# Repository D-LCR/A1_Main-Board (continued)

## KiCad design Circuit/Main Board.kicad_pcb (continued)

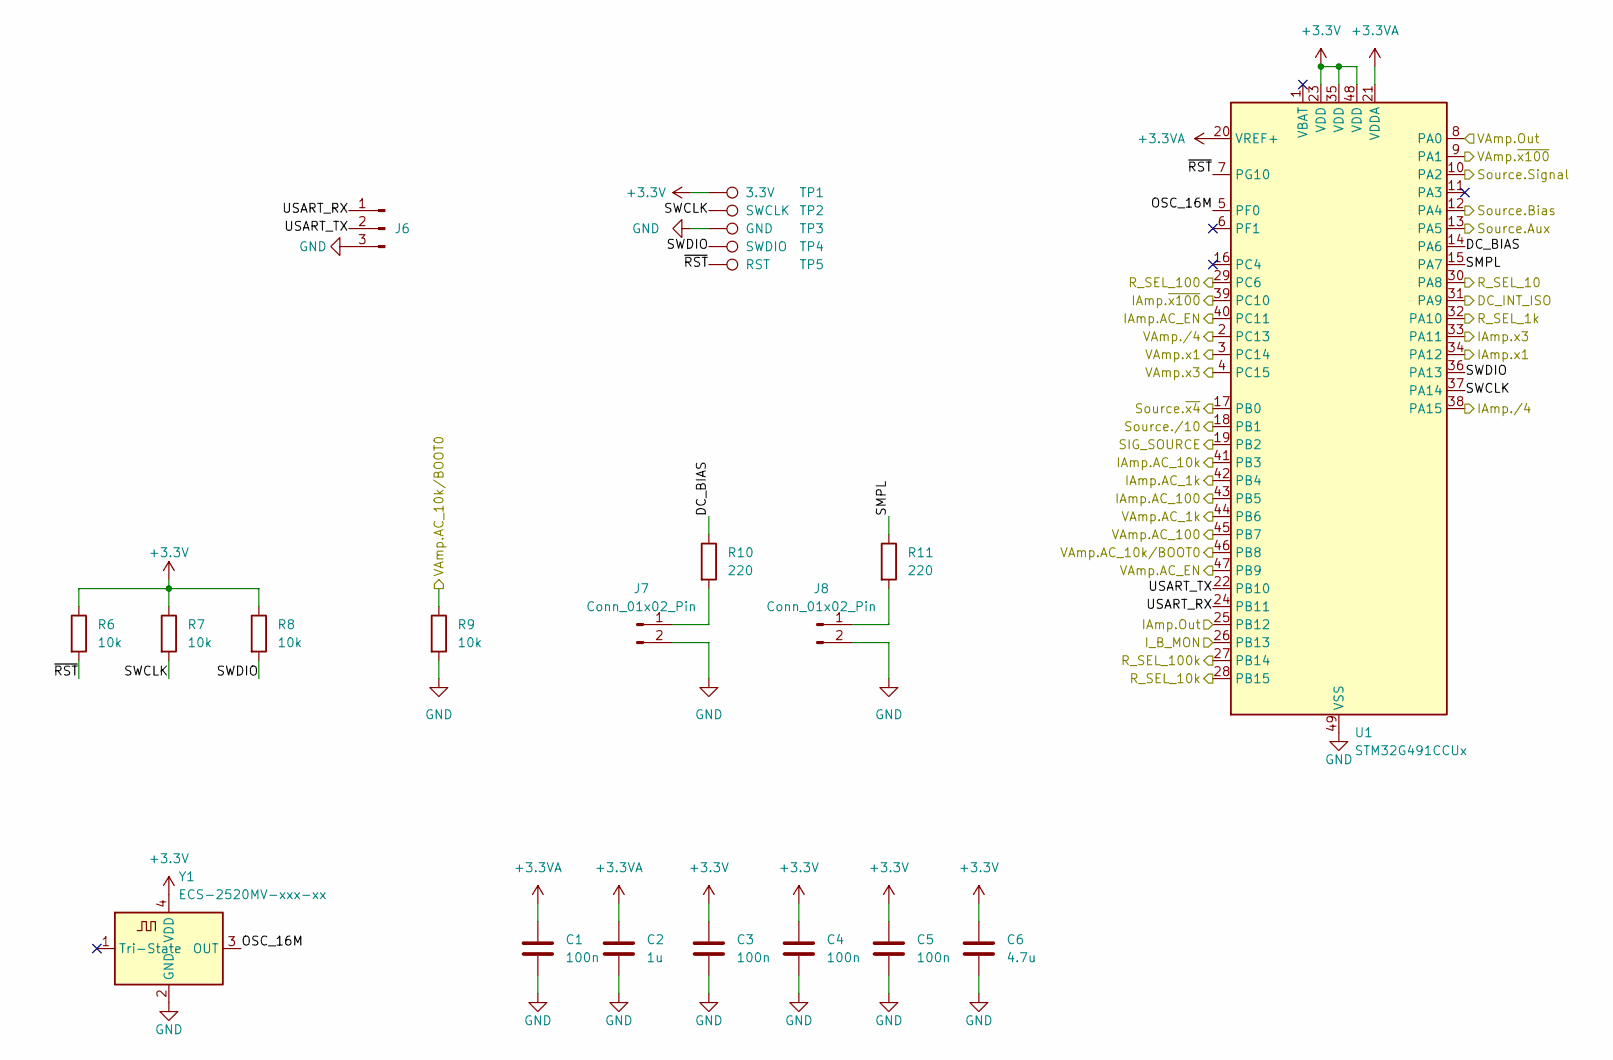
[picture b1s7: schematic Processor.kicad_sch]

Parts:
C1, C3, C4, C5: 100n; C_0805_2012Metric
C2: 1u; C_0805_2012Metric
C6: 4.7u; C_0805_2012Metric
J6: Conn_01x03_Pin; Molex_KK-254_AE-6410-03A_1x03_P2.54mm_Vertical
J7, J8: Conn_01x02_Pin; Molex_KK-254_AE-6410-02A_1x02_P2.54mm_Vertical
R6, R7, R8, R9: 10k; R_0805_2012Metric
R10, R11: 220; R_0805_2012Metric
TP1: 3.3V; TestPoint_Pad_2.0x2.0mm
TP2: SWCLK; TestPoint_Pad_2.0x2.0mm
TP3: GND; TestPoint_Pad_2.0x2.0mm
TP4: SWDIO; TestPoint_Pad_2.0x2.0mm
TP5: RST; TestPoint_Pad_2.0x2.0mm
U1: STM32G491CCUx; QFN-48-1EP_7x7mm_P0.5mm_EP5.6x5.6mm
Y1: ECS-2520MV-xxx-xx; Oscillator_SMD_ECS_2520MV-xxx-xx-4Pin_2.5x2.0mm

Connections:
+3.3V: C3.1, C4.1, C5.1, C6.1, R6.1, R7.1, R8.1, TP1.1 (1_1), U1.23 (VDD), U1.35 (VDD), U1.48 (VDD), Y1.4 (VDD); also elsewhere on the board
+3.3VA: C1.1, C2.1, U1.20 (VREF+), U1.21 (VDDA); also elsewhere on the board
/Auto-Balancing Bridge/AC_1k: U1.43 (PB5); also elsewhere on the board
/Auto-Balancing Bridge/AC_10k: U1.41 (PB3); also elsewhere on the board
/Auto-Balancing Bridge/AC_100: U1.42 (PB4); also elsewhere on the board
/Auto-Balancing Bridge/AC_EN: U1.40 (PC11); also elsewhere on the board
/Auto-Balancing Bridge/DC_INT_ISO: U1.31 (PA9); also elsewhere on the board
/Auto-Balancing Bridge/I_B_MONITOR: U1.26 (PB13); also elsewhere on the board
/Auto-Balancing Bridge/R_SEL_1k: U1.32 (PA10); also elsewhere on the board
/Auto-Balancing Bridge/R_SEL_10: U1.30 (PA8); also elsewhere on the board
/Auto-Balancing Bridge/R_SEL_10k: U1.28 (PB15); also elsewhere on the board
/Auto-Balancing Bridge/R_SEL_100: U1.29 (PC6); also elsewhere on the board
/Auto-Balancing Bridge/R_SEL_100k: U1.27 (PB14); also elsewhere on the board
/Current Amplifier/Out: U1.25 (PB12); also elsewhere on the board
/Current Amplifier/x1: U1.34 (PA12); also elsewhere on the board
/Current Amplifier/x3: U1.33 (PA11); also elsewhere on the board
/Current Amplifier//4: U1.38 (PA15); also elsewhere on the board
/Current Amplifier/~x100: U1.39 (PC10); also elsewhere on the board
/Processor/DC_BIAS: R10.1, U1.14 (PA6)
/Processor/OSC_16M: U1.5 (PF0), Y1.3 (OUT)
/Processor/SIG_SOURCE: U1.19 (PB2); also elsewhere on the board
/Processor/SMPL: R11.1, U1.15 (PA7)
/Processor/SWCLK: R7.2, TP2.1 (1_1), U1.37 (PA14)
/Processor/SWDIO: R8.2, TP4.1 (1_1), U1.36 (PA13)
/Processor/Source.Aux: U1.13 (PA5); also elsewhere on the board
/Processor/Source.Bias: U1.12 (PA4); also elsewhere on the board
/Processor/Source.Signal: U1.10 (PA2); also elsewhere on the board
/Processor/Source./10: U1.18 (PB1); also elsewhere on the board
/Processor/Source.~x4: U1.17 (PB0); also elsewhere on the board
/Processor/USART_RX: J6.1, U1.24 (PB11)
/Processor/USART_TX: J6.2, U1.22 (PB10)
/Processor/VAmp.AC_1k: U1.44 (PB6); also elsewhere on the board
/Processor/VAmp.AC_10k/BOOT0: R9.1, U1.46 (PB8); also elsewhere on the board
/Processor/VAmp.AC_100: U1.45 (PB7); also elsewhere on the board
/Processor/VAmp.AC_EN: U1.47 (PB9); also elsewhere on the board
/Processor/VAmp.Out: U1.8 (PA0); also elsewhere on the board
/Processor/VAmp.x1: U1.3 (PC14); also elsewhere on the board
/Processor/VAmp.x3: U1.4 (PC15); also elsewhere on the board
/Processor/VAmp./4: U1.2 (PC13); also elsewhere on the board
/Processor/VAmp.~x100: U1.9 (PA1); also elsewhere on the board
/Processor/~RST: R6.2, TP5.1 (1_1), U1.7 (PG10)
GND: C1.2, C2.2, C3.2, C4.2, C5.2, C6.2, J6.3, J7.2, J8.2, R9.2, TP3.1 (1_1), U1.49 (VSS), Y1.2 (GND); also elsewhere on the board
unnamed: J7.1, R10.2
unnamed: J8.1, R11.2

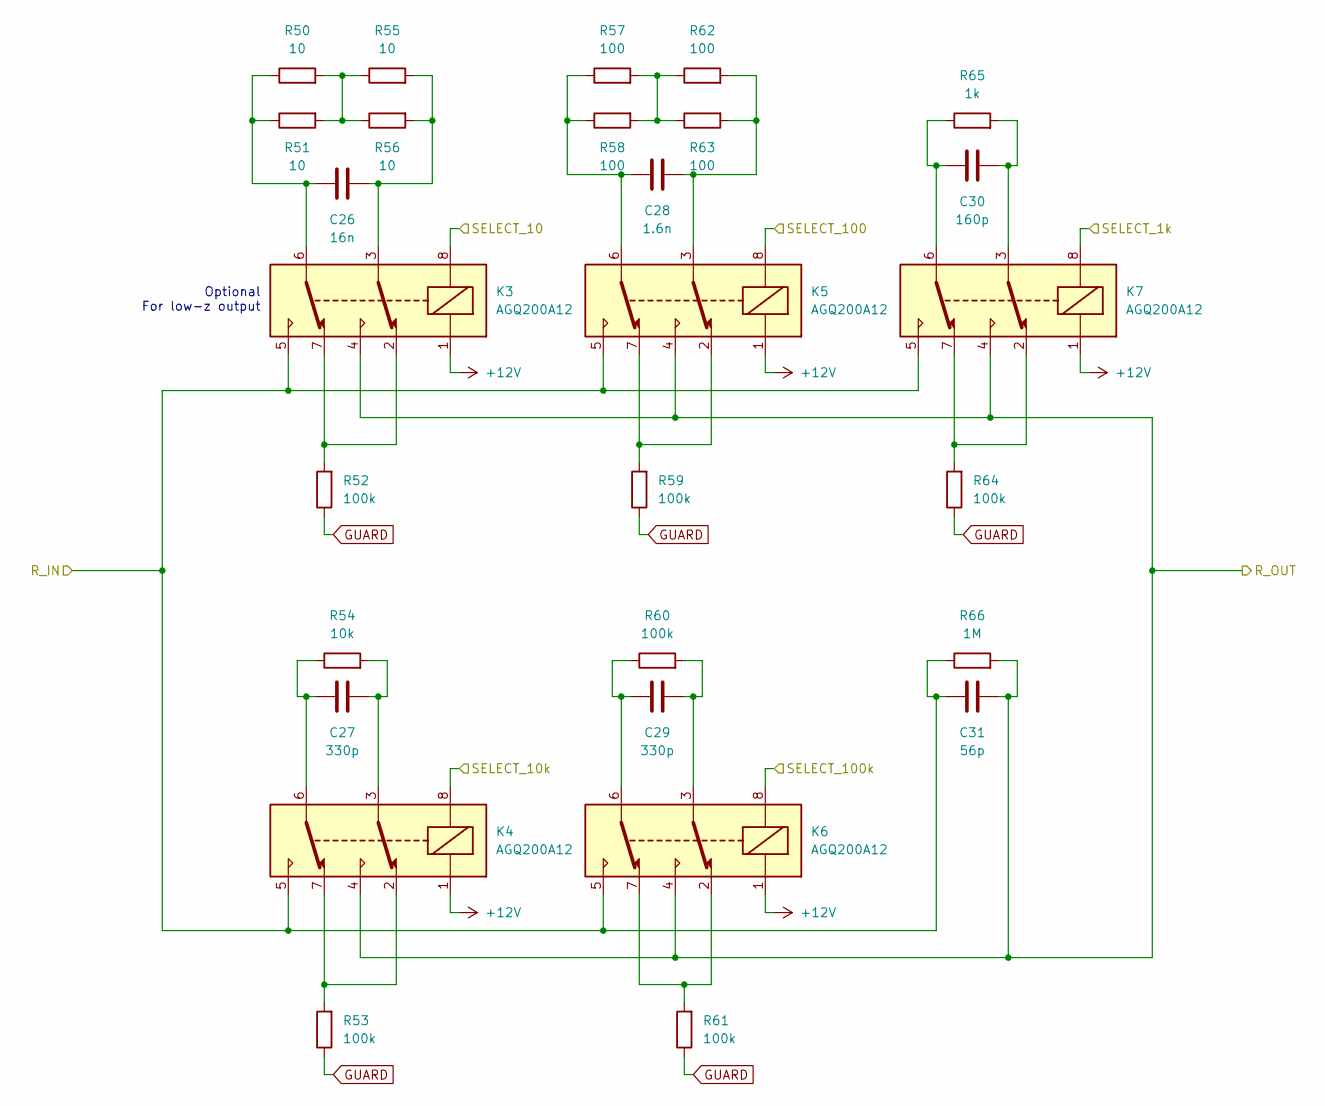
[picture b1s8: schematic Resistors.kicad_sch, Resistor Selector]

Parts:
C26: 16n; C_0805_2012Metric
C27, C29: 330p; C_0805_2012Metric
C28: 1.6n; C_0805_2012Metric
C30: 160p; C_0805_2012Metric
C31: 56p; C_0805_2012Metric
K3, K4, K5, K6, K7: AGQ200A12; RELAY_AGQ_A_PAN; Mouser Part Number 769-AGQ200A12
R50, R51, R55, R56: 10; R_2512_6332Metric
R52, R53, R59, R60, R61, R64: 100k; R_0805_2012Metric
R54: 10k; R_0805_2012Metric
R57, R58, R62, R63: 100; R_0805_2012Metric
R65: 1k; R_0805_2012Metric
R66: 1M; R_0805_2012Metric

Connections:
+12V: K3.1, K4.1, K5.1, K6.1, K7.1; also elsewhere on the board
/Auto-Balancing Bridge/OUT+: C31.2, K3.4, K4.4, K5.4, K6.4, K7.4, R66.2; also elsewhere on the board
/Auto-Balancing Bridge/SEL_1k: K7.8; also elsewhere on the board
/Auto-Balancing Bridge/SEL_10: K3.8; also elsewhere on the board
/Auto-Balancing Bridge/SEL_10k: K4.8; also elsewhere on the board
/Auto-Balancing Bridge/SEL_100: K5.8; also elsewhere on the board
/Auto-Balancing Bridge/SEL_100k: K6.8; also elsewhere on the board
/Auto-Balancing Bridge/TIA_SUM: C31.1, K3.5, K4.5, K5.5, K6.5, K7.5, R66.1; also elsewhere on the board
GUARD: R52.1, R53.1, R59.1, R61.1, R64.1; also elsewhere on the board
unnamed: C26.1, K3.6, R50.1, R51.1
unnamed: C26.2, K3.3, R55.2, R56.2
unnamed: C27.1, K4.6, R54.1
unnamed: C27.2, K4.3, R54.2
unnamed: C28.1, K5.6, R57.1, R58.1
unnamed: C28.2, K5.3, R62.2, R63.2
unnamed: C29.1, K6.6, R60.1
unnamed: C29.2, K6.3, R60.2
unnamed: C30.1, K7.6, R65.1
unnamed: C30.2, K7.3, R65.2
unnamed: K3.2, K3.7, R52.2
unnamed: K4.2, K4.7, R53.2
unnamed: K5.2, K5.7, R59.2
unnamed: K6.2, K6.7, R61.2
unnamed: K7.2, K7.7, R64.2
unnamed: R50.2, R51.2, R55.1, R56.1
unnamed: R57.2, R58.2, R62.1, R63.1

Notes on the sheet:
Optional For low-z output

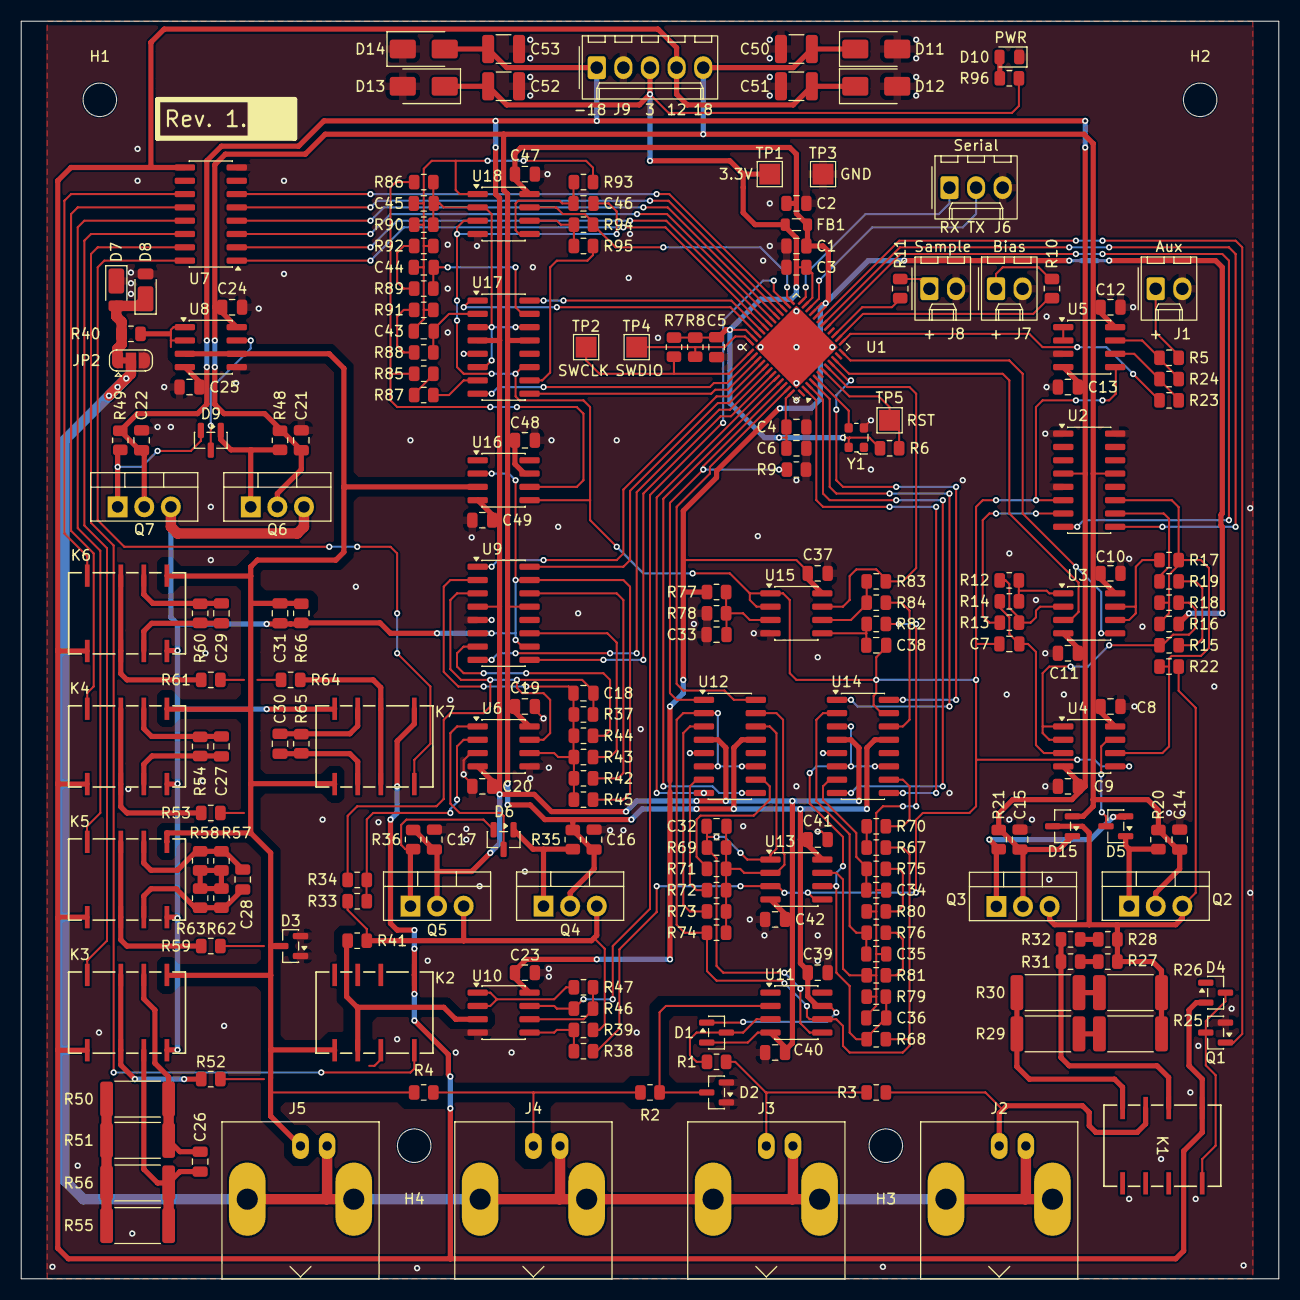
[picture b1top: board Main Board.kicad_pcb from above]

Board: 2 copper layers, 120.0 x 120.0 mm, 217 parts (0 on the bottom side), 154 nets.

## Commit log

2026-05-02 Output job, Revision Box and reorganise
2026-05-02 Update jobset
2026-05-04 Input Protection Second Attempt
2026-05-04 New Resistor Selection Circuit
2026-05-04 Fix Soldermask Errors
2026-05-05 Migrate to KiCAD V10
2026-05-05 Adjustments
2026-05-05 Final Touches
2026-05-05 Issue
2026-05-24 Update Output Job
